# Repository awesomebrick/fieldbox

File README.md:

# fieldbox
Senior design project. FPGA-powered eurorack synthesis and audio processing module

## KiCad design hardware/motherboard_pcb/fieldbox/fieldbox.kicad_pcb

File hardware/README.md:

# Sorry for the mess.
Will sort things properly when I get the chance.

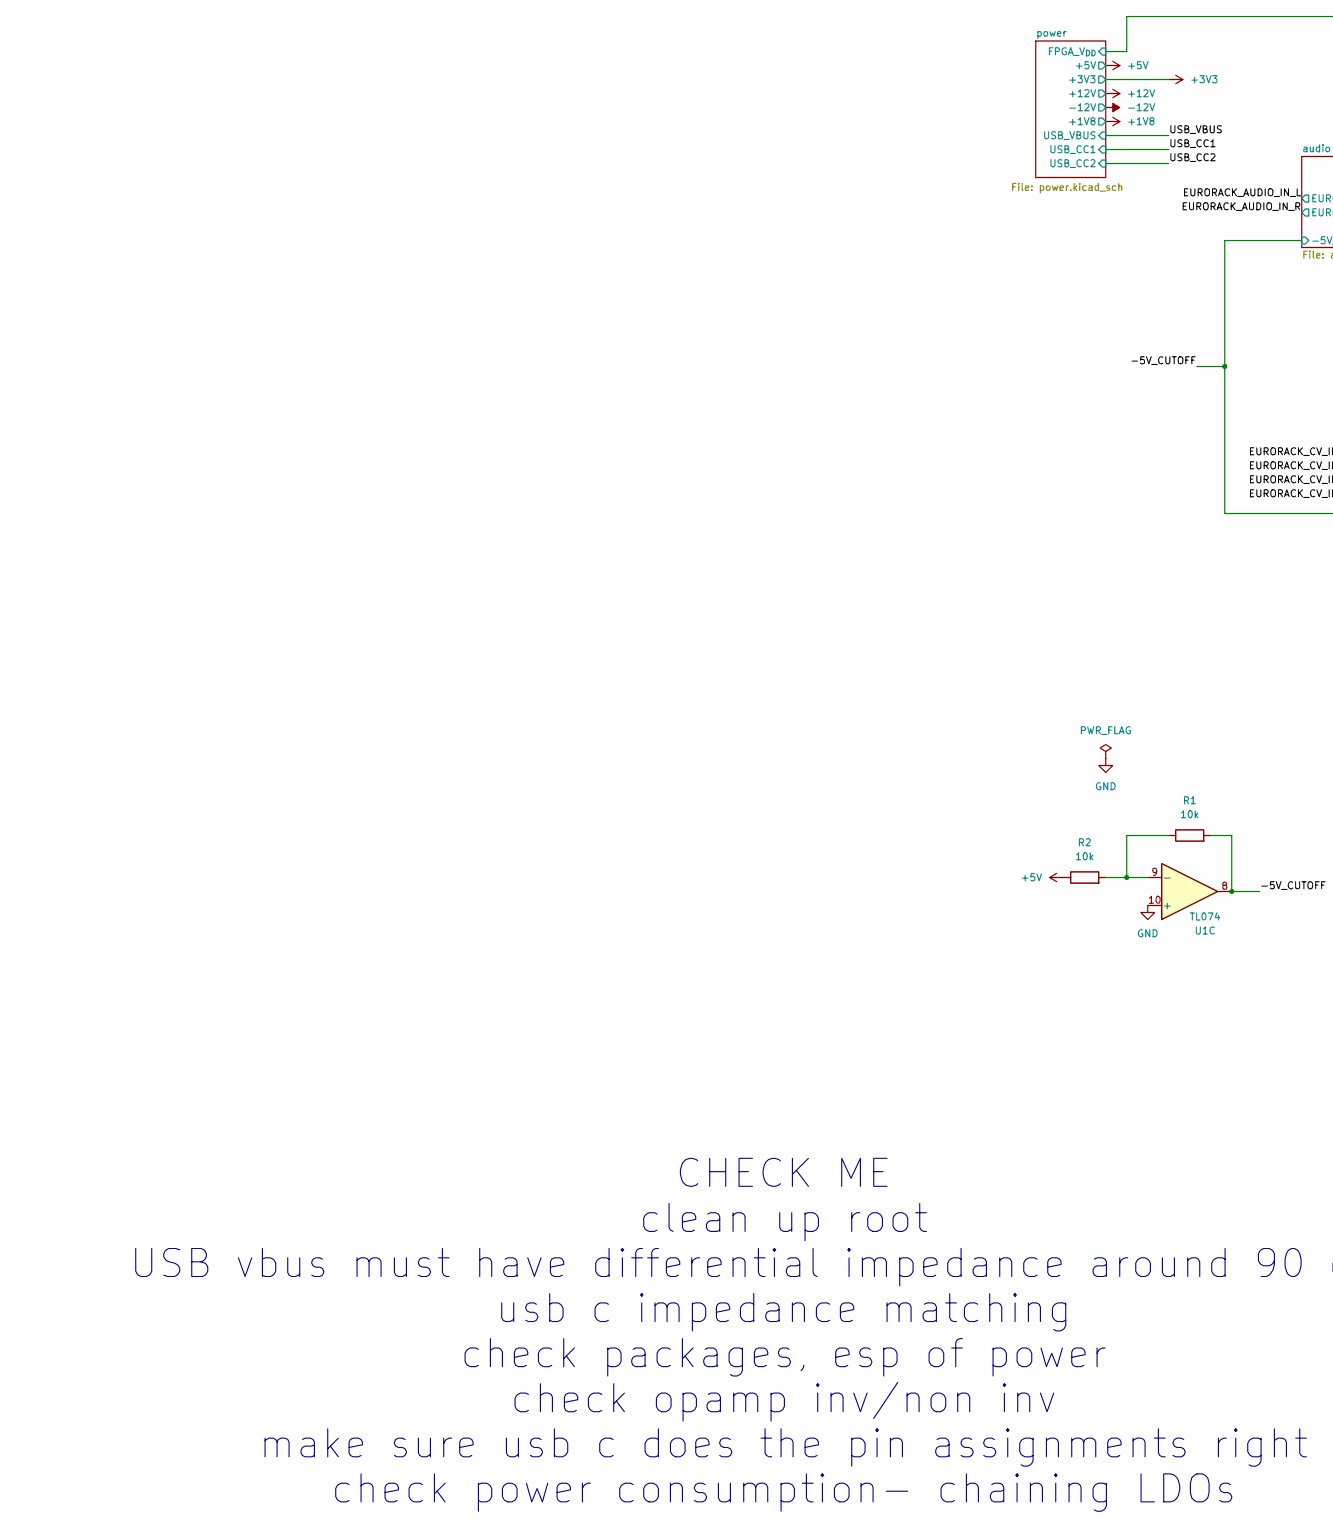
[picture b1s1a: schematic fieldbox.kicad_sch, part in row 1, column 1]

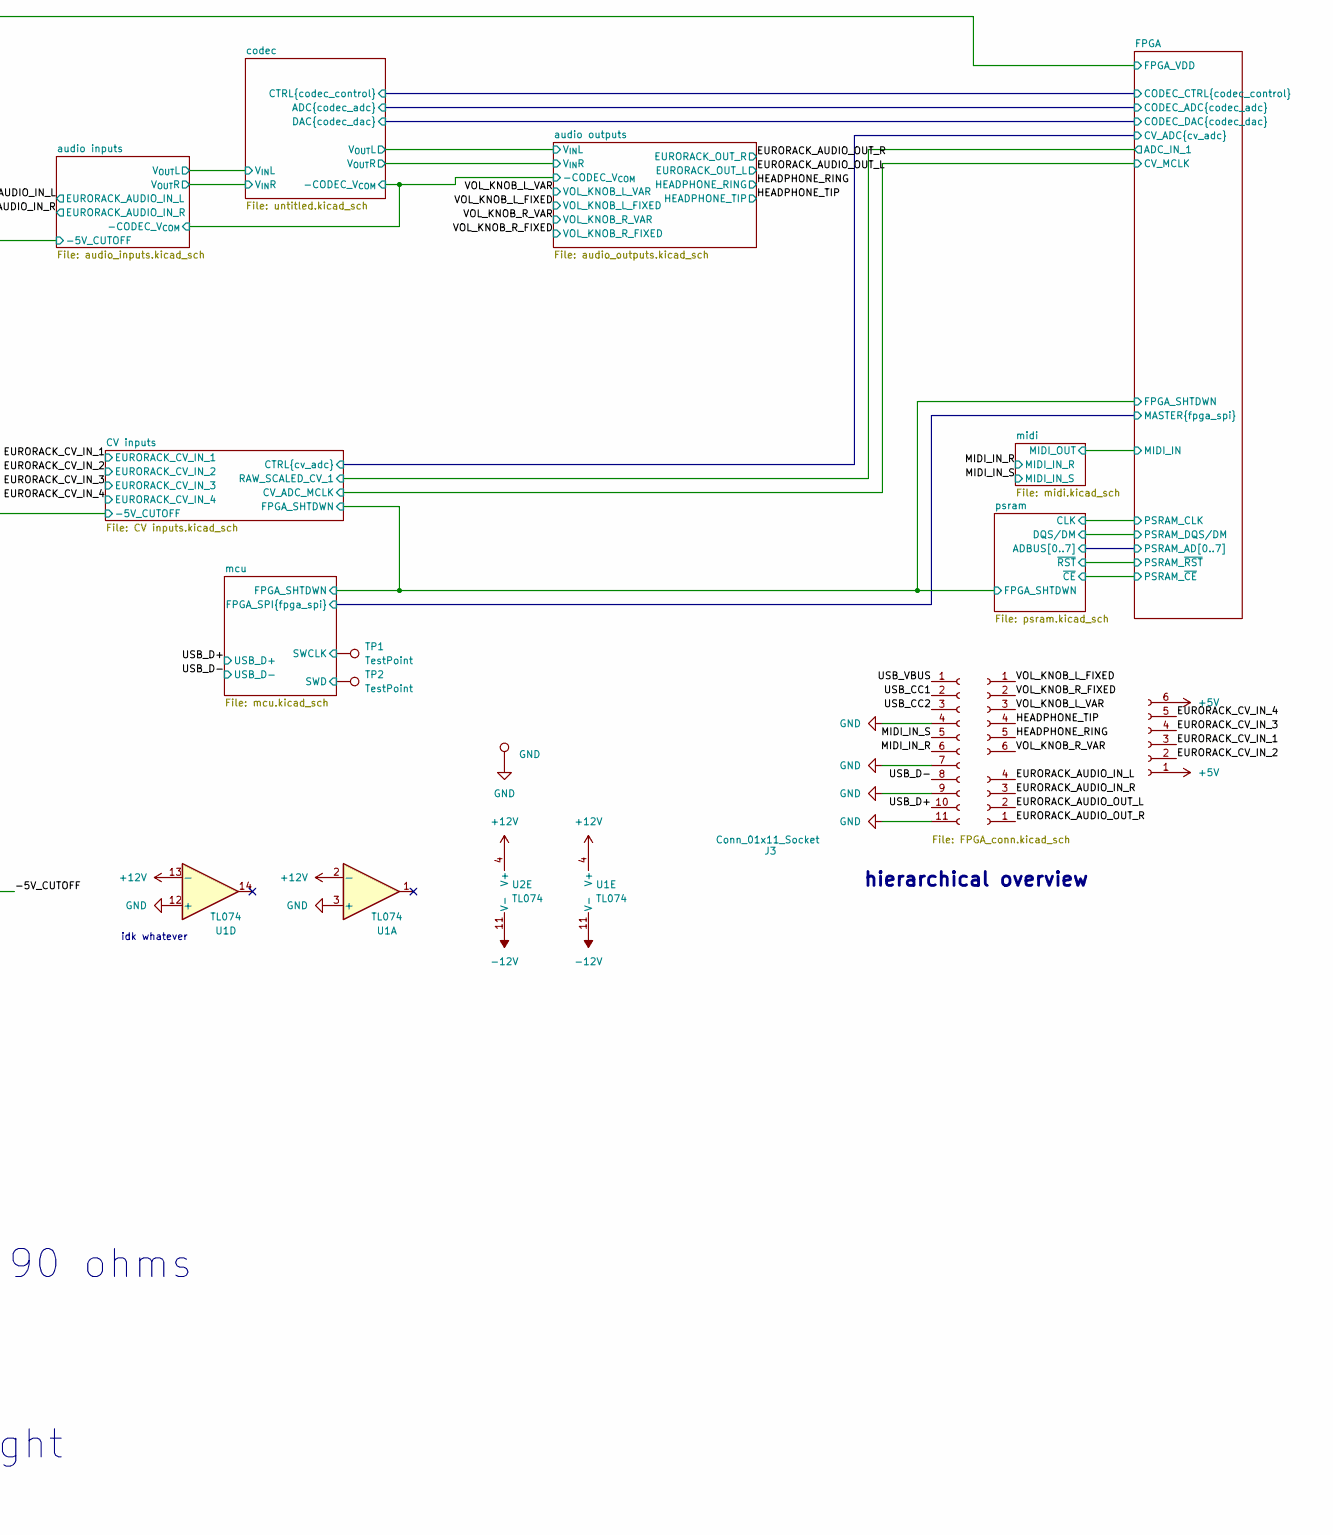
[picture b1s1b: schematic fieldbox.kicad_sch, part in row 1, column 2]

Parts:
J1: Conn_01x04_Socket; PinSocket_1x06_P2.54mm_Vertical
J2: Conn_01x06_Socket; PinSocket_1x06_P2.54mm_Vertical
J3: Conn_01x11_Socket; PinSocket_1x11_P2.54mm_Vertical
J5: Conn_01x04_Socket; PinSocket_1x04_P2.54mm_Vertical
R1, R2: 10k; R_0603_1608Metric; Mouser # 652-CRT0603BY1002ELF
TP1, TP2: TestPoint; TestPoint_Pad_2.0x2.0mm; Mouser # NA
TP3: GND; TestPoint_Pad_D2.0mm; Mouser # NA
U1, U2: TL074; TSSOP-14_4.4x5mm_P0.65mm; Mouser # 595-TL074HIPWR

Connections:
+5V: J1.1, J1.6, R2.1; also elsewhere on the board
+12V: U1.2 (-), U1.4 (V+), U1.13 (-), U2.4 (V+); also elsewhere on the board
-12V: U1.11 (V-), U2.11 (V-); also elsewhere on the board
/-5V_CUTOFF: R1.2, U1.8; also elsewhere on the board
/EURORACK_AUDIO_IN_L: J5.4; also elsewhere on the board
/EURORACK_AUDIO_IN_R: J5.3; also elsewhere on the board
/EURORACK_AUDIO_OUT_L: J5.2; also elsewhere on the board
/EURORACK_AUDIO_OUT_R: J5.1; also elsewhere on the board
/EURORACK_CV_IN_1: J1.3; also elsewhere on the board
/EURORACK_CV_IN_2: J1.2; also elsewhere on the board
/EURORACK_CV_IN_3: J1.4; also elsewhere on the board
/EURORACK_CV_IN_4: J1.5; also elsewhere on the board
/HEADPHONE_RING: J2.5; also elsewhere on the board
/HEADPHONE_TIP: J2.4; also elsewhere on the board
/MIDI_IN_R: J3.6; also elsewhere on the board
/MIDI_IN_S: J3.5; also elsewhere on the board
/USB_CC1: J3.2; also elsewhere on the board
/USB_CC2: J3.3; also elsewhere on the board
/USB_D+: J3.10; also elsewhere on the board
/USB_D-: J3.8; also elsewhere on the board
/USB_VBUS: J3.1; also elsewhere on the board
/VOL_KNOB_L_FIXED: J2.1; also elsewhere on the board
/VOL_KNOB_L_VAR: J2.3; also elsewhere on the board
/VOL_KNOB_R_FIXED: J2.2; also elsewhere on the board
/VOL_KNOB_R_VAR: J2.6; also elsewhere on the board
/mcu/SWCLK: TP1.1; also elsewhere on the board
/mcu/SWD: TP2.1; also elsewhere on the board
GND: J3.4, J3.7, J3.9, J3.11, TP3.1, U1.3 (+), U1.10 (+), U1.12 (+); also elsewhere on the board
unnamed: R1.1, R2.2, U1.9 (-)

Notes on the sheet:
hierarchical overview
CHECK ME clean up root USB vbus must have differential impedance around 90 ohms usb c impedance matching check packages, esp of power check opamp inv/non inv make sure usb c does the pin assignments right check power consumption- chaining LDOs
idk whatever

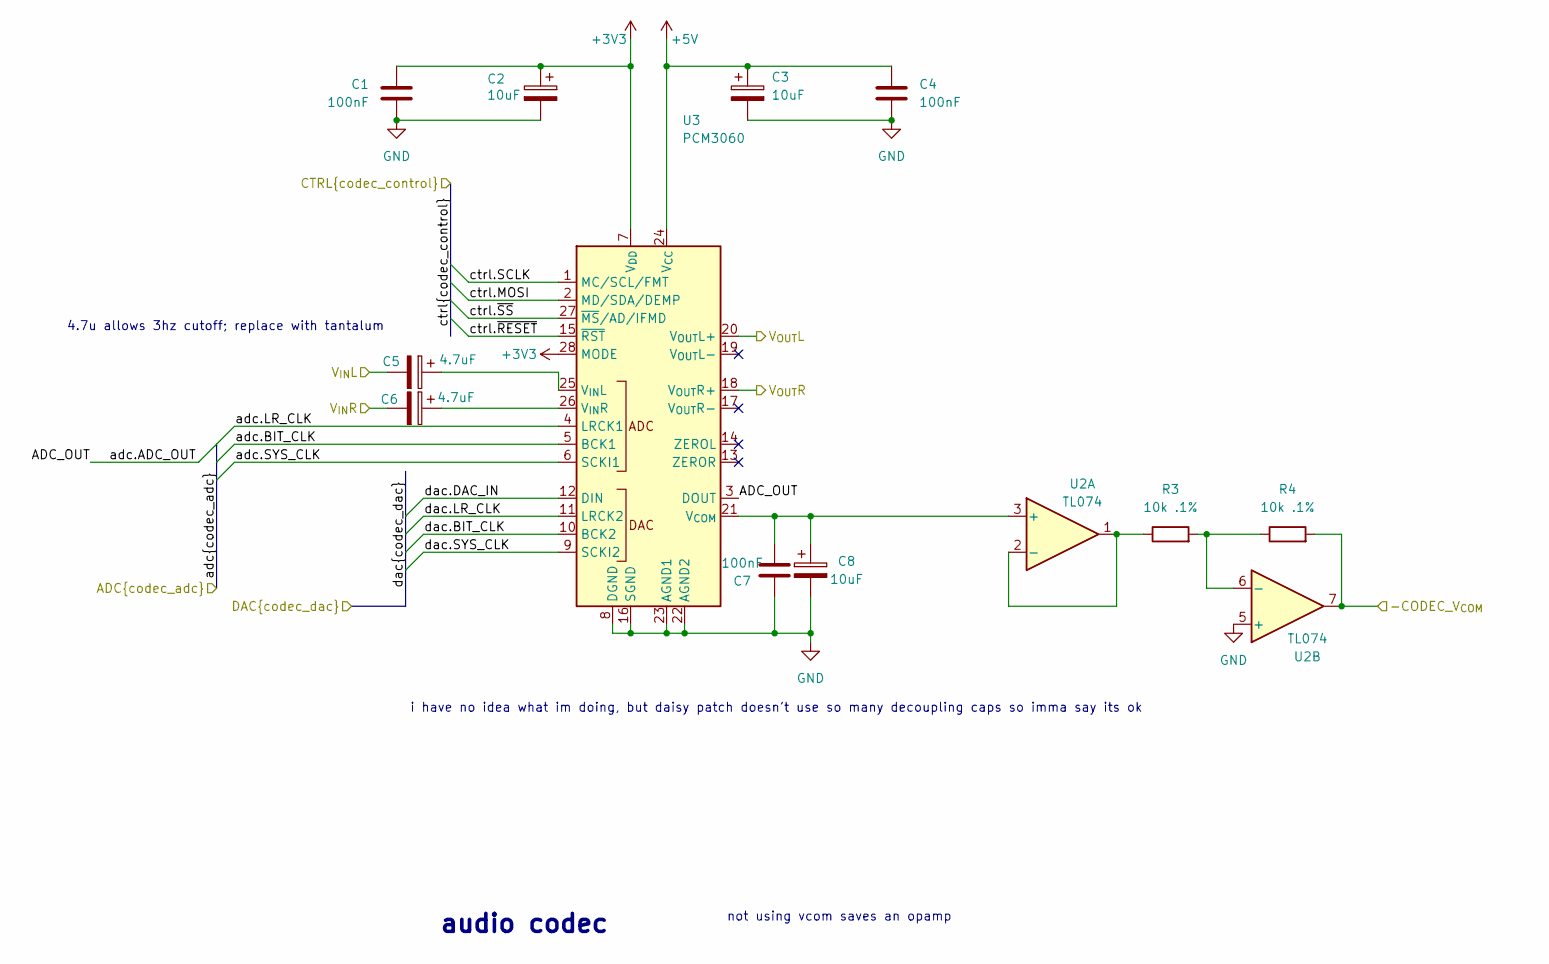
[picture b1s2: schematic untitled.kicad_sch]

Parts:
C1, C4, C7: 100nF; C_0603_1608Metric; Mouser # KGM15AR71C104MM
C2, C3, C8: 10uF; CP_EIA-3216-18_Kemet-A; Mouser # 581-TAJA106K016R
C5, C6: 4.7uF; CP_EIA-3216-18_Kemet-A; Mouser # 581-TAJA475M006R
R3, R4: 10k .1%; R_0603_1608Metric; Mouser # 652-CRT0603BY1002ELF
U2: TL074; TSSOP-14_4.4x5mm_P0.65mm; Mouser # 595-TL074HIPWR
U3: PCM3060; TSSOP-28_4.4x9.7mm_P0.65mm; Mouser # PCM3060PWR

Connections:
+3V3: C1.1, C2.1, U3.7 (V_{DD}), U3.28 (MODE); also elsewhere on the board
+5V: C3.1, C4.1, U3.24 (V_{CC}); also elsewhere on the board
/FPGA/CODEC_ADC.ADC_OUT: U3.3 (DOUT); also elsewhere on the board
/FPGA/CODEC_ADC.BIT_CLK: U3.5 (BCK1); also elsewhere on the board
/FPGA/CODEC_ADC.LR_CLK: U3.4 (LRCK1); also elsewhere on the board
/FPGA/CODEC_ADC.SYS_CLK: U3.6 (SCKI1); also elsewhere on the board
/FPGA/CODEC_CTRL.MOSI: U3.2 (MD/SDA/DEMP); also elsewhere on the board
/FPGA/CODEC_CTRL.SCLK: U3.1 (MC/SCL/FMT); also elsewhere on the board
/FPGA/CODEC_CTRL.~RESET: U3.15 (~RST); also elsewhere on the board
/FPGA/CODEC_CTRL.~SS: U3.27 (~MS/AD/IFMD); also elsewhere on the board
/FPGA/CODEC_DAC.BIT_CLK: U3.10 (BCK2); also elsewhere on the board
/FPGA/CODEC_DAC.DAC_IN: U3.12 (DIN); also elsewhere on the board
/FPGA/CODEC_DAC.LR_CLK: U3.11 (LRCK2); also elsewhere on the board
/FPGA/CODEC_DAC.SYS_CLK: U3.9 (SCKI2); also elsewhere on the board
/audio inputs/-CODEC_V_{COM}: R4.2, U2.7; also elsewhere on the board
/audio inputs/V_{OUT}L: C5.2; also elsewhere on the board
/audio inputs/V_{OUT}R: C6.2; also elsewhere on the board
/audio outputs/V_{IN}L: U3.20 (V_{OUT}L+); also elsewhere on the board
/audio outputs/V_{IN}R: U3.18 (V_{OUT}R+); also elsewhere on the board
GND: C1.2, C2.2, C3.2, C4.2, C7.1, C8.2, U2.5 (+), U3.8 (DGND), U3.16 (SGND), U3.22 (AGND2), U3.23 (AGND1); also elsewhere on the board
unnamed: C7.2, C8.1, U2.3 (+), U3.21 (V_{COM})
unnamed: R3.1, U2.1, U2.2 (-)
unnamed: R3.2, R4.1, U2.6 (-)
unnamed: C5.1, U3.25 (V_{IN}L)
unnamed: C6.1, U3.26 (V_{IN}R)

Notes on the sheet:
i have no idea what im doing, but daisy patch doesn't use so many decoupling caps so imma say its ok
4.7u allows 3hz cutoff; replace with tantalum
not using vcom saves an opamp
audio codec

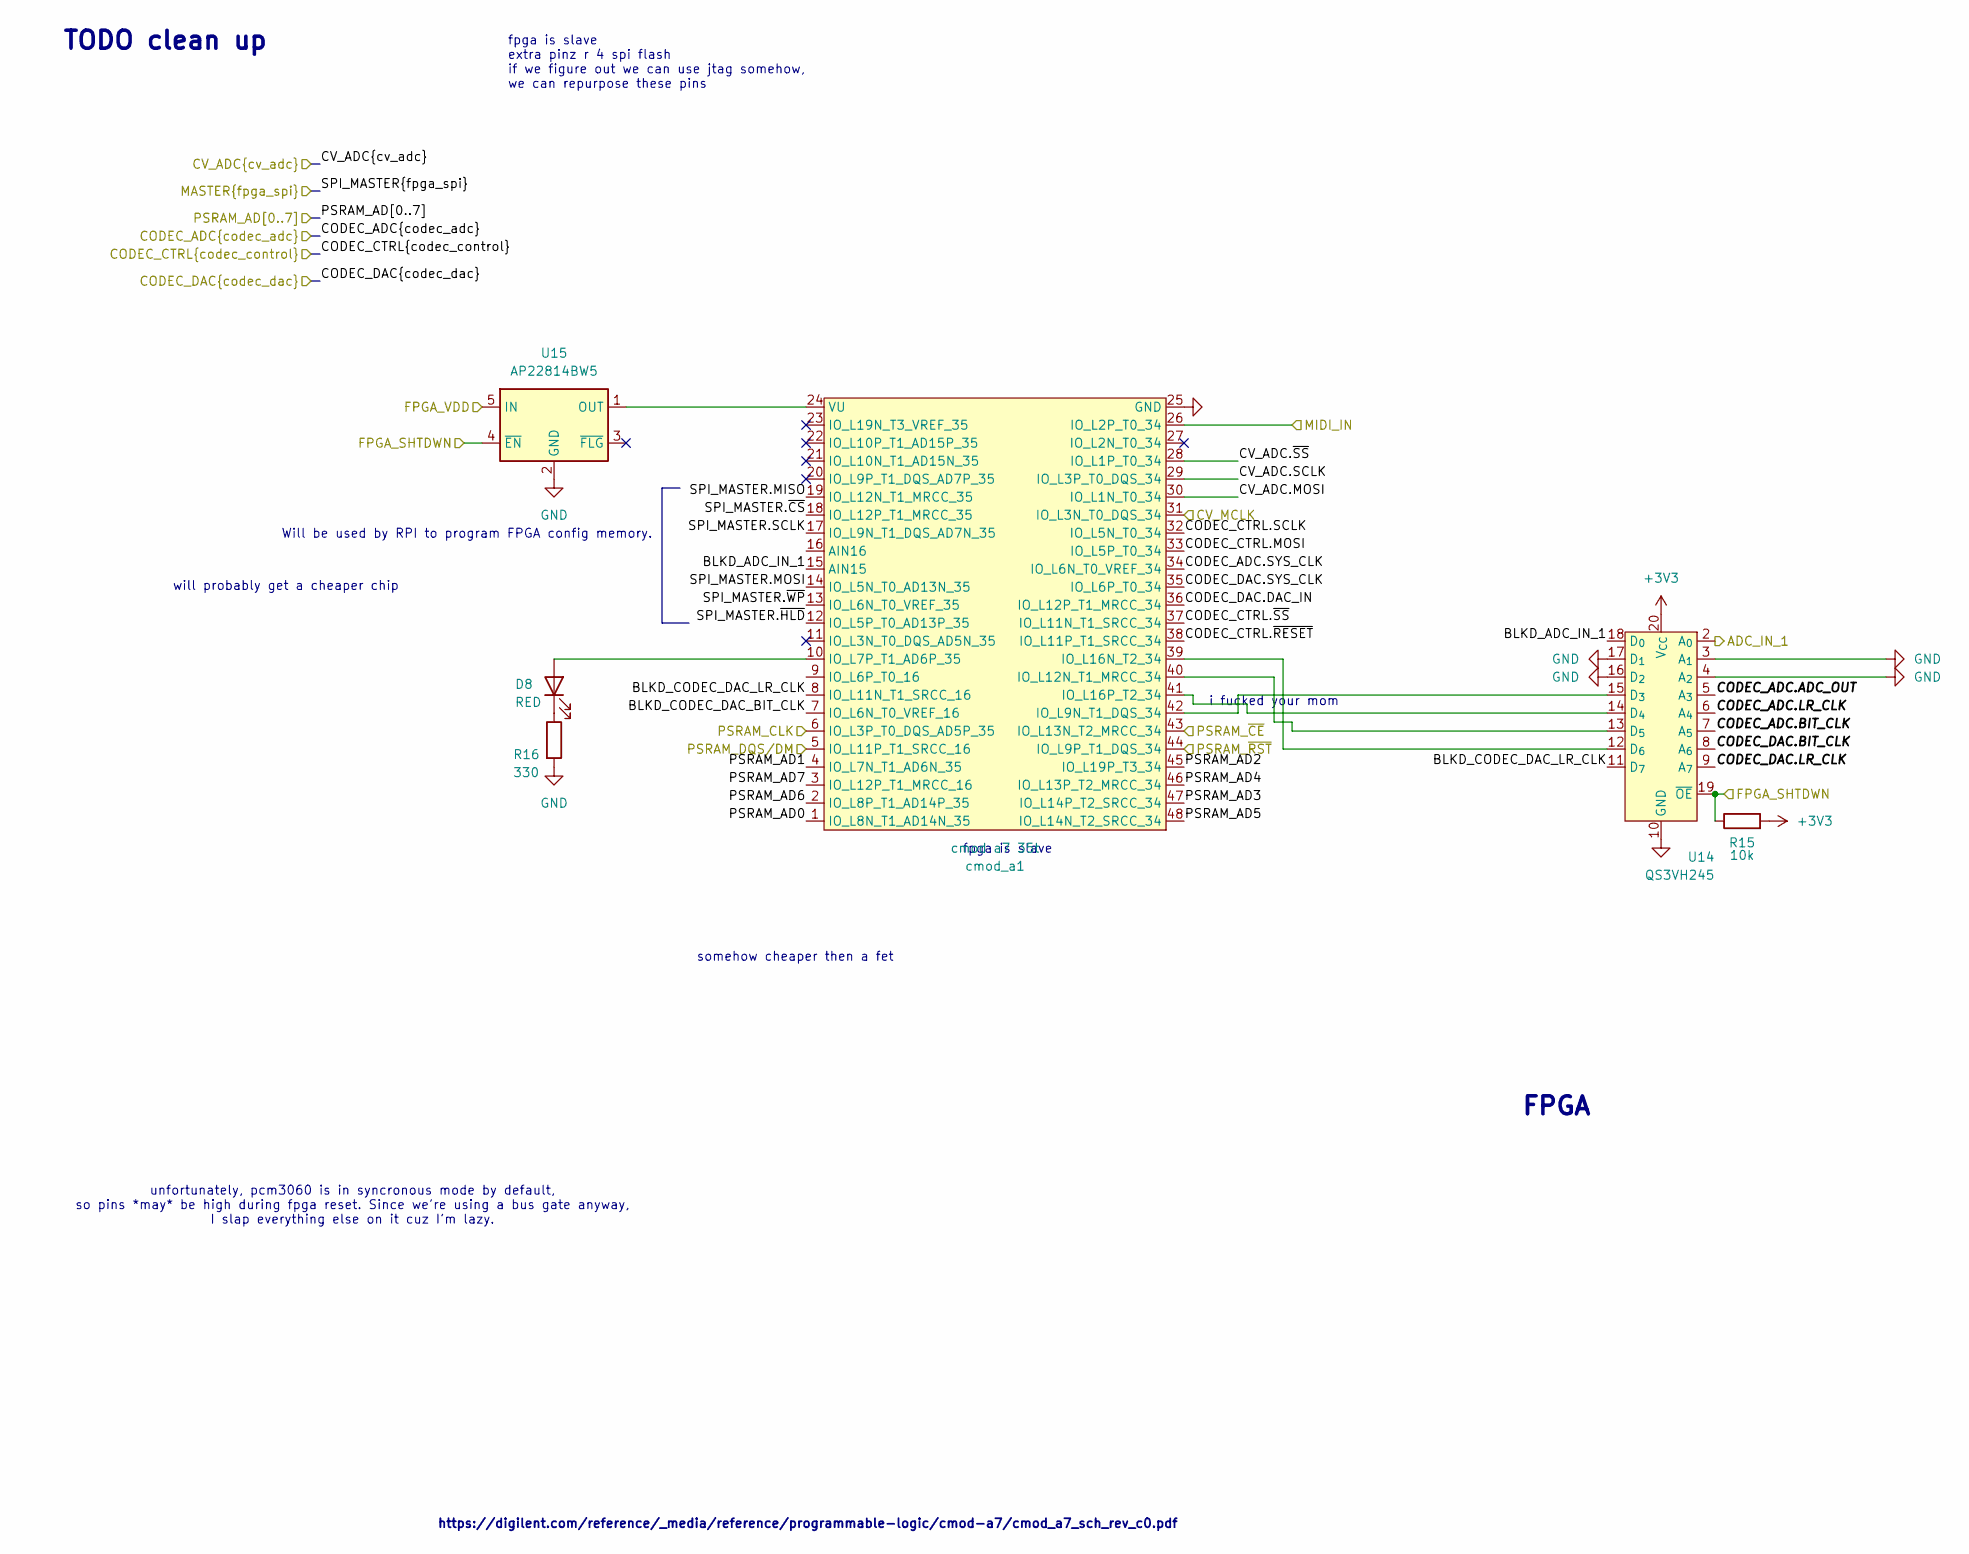
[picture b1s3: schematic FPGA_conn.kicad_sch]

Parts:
D8: RED; LED_0603_1608Metric; Mouser # 720-LSQ976.01-N1Q2-1
R15: 10k; R_0603_1608Metric; Mouser # 652-CRT0603BY1002ELF
R16: 330; R_0603_1608Metric; Mouser # 603-RC0603FR-10330RL
U14: QS3VH245; QSOP-20_3.9x8.7mm_P0.635mm; Mouser # 972-QS3VH245QG8
U15: AP22814BW5; SOT-23-5; Mouser # 621-AP22814BW5-7
cmod_a1: cmod a7 35t; CMOD-A7; Mouser # 424-410-328-35

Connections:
+3V3: R15.2, U14.20 (V_{CC}); also elsewhere on the board
/CV inputs/CV_ADC_MCLK: cmod_a1.31 (IO_L3N_T0_DQS_34); also elsewhere on the board
/CV inputs/FPGA_SHTDWN: R15.1, U14.19 (~OE), U15.4 (~EN); also elsewhere on the board
/CV inputs/RAW_SCALED_CV_1: U14.2 (A_{0}); also elsewhere on the board
/CV inputs/adc.MOSI: cmod_a1.30 (IO_L1N_T0_34); also elsewhere on the board
/CV inputs/adc.SCLK: cmod_a1.29 (IO_L3P_T0_DQS_34); also elsewhere on the board
/CV inputs/adc.~SS: cmod_a1.28 (IO_L1P_T0_34); also elsewhere on the board
/FPGA/BLKD_ADC_IN_1: U14.18 (D_{0}), cmod_a1.15 (AIN15)
/FPGA/BLKD_CODEC_DAC_BIT_CLK: cmod_a1.7 (IO_L6N_T0_VREF_16)
/FPGA/BLKD_CODEC_DAC_LR_CLK: U14.11 (D_{7}), cmod_a1.8 (IO_L11N_T1_SRCC_16)
/FPGA/CODEC_ADC.ADC_OUT: U14.5 (A_{3}); also elsewhere on the board
/FPGA/CODEC_ADC.BIT_CLK: U14.7 (A_{5}); also elsewhere on the board
/FPGA/CODEC_ADC.LR_CLK: U14.6 (A_{4}); also elsewhere on the board
/FPGA/CODEC_ADC.SYS_CLK: cmod_a1.34 (IO_L6N_T0_VREF_34); also elsewhere on the board
/FPGA/CODEC_CTRL.MOSI: cmod_a1.33 (IO_L5P_T0_34); also elsewhere on the board
/FPGA/CODEC_CTRL.SCLK: cmod_a1.32 (IO_L5N_T0_34); also elsewhere on the board
/FPGA/CODEC_CTRL.~RESET: cmod_a1.38 (IO_L11P_T1_SRCC_34); also elsewhere on the board
/FPGA/CODEC_CTRL.~SS: cmod_a1.37 (IO_L11N_T1_SRCC_34); also elsewhere on the board
/FPGA/CODEC_DAC.BIT_CLK: U14.8 (A_{6}); also elsewhere on the board
/FPGA/CODEC_DAC.DAC_IN: cmod_a1.36 (IO_L12P_T1_MRCC_34); also elsewhere on the board
/FPGA/CODEC_DAC.LR_CLK: U14.9 (A_{7}); also elsewhere on the board
/FPGA/CODEC_DAC.SYS_CLK: cmod_a1.35 (IO_L6P_T0_34); also elsewhere on the board
/FPGA/FPGA_VDD: U15.5 (IN); also elsewhere on the board
/FPGA/MIDI_IN: cmod_a1.26 (IO_L2P_T0_34); also elsewhere on the board
/FPGA/PSRAM_AD0: cmod_a1.1 (IO_L8N_T1_AD14N_35); also elsewhere on the board
/FPGA/PSRAM_AD1: cmod_a1.4 (IO_L7N_T1_AD6N_35); also elsewhere on the board
/FPGA/PSRAM_AD2: cmod_a1.45 (IO_L19P_T3_34); also elsewhere on the board
/FPGA/PSRAM_AD3: cmod_a1.47 (IO_L14P_T2_SRCC_34); also elsewhere on the board
/FPGA/PSRAM_AD4: cmod_a1.46 (IO_L13P_T2_MRCC_34); also elsewhere on the board
/FPGA/PSRAM_AD5: cmod_a1.48 (IO_L14N_T2_SRCC_34); also elsewhere on the board
/FPGA/PSRAM_AD6: cmod_a1.2 (IO_L8P_T1_AD14P_35); also elsewhere on the board
/FPGA/PSRAM_AD7: cmod_a1.3 (IO_L12P_T1_MRCC_16); also elsewhere on the board
/FPGA/PSRAM_CLK: cmod_a1.6 (IO_L3P_T0_DQS_AD5P_35); also elsewhere on the board
/FPGA/PSRAM_DQS/DM: cmod_a1.5 (IO_L11P_T1_SRCC_16); also elsewhere on the board
/FPGA/PSRAM_~CE: cmod_a1.43 (IO_L13N_T2_MRCC_34); also elsewhere on the board
/FPGA/PSRAM_~RST: cmod_a1.44 (IO_L9P_T1_DQS_34); also elsewhere on the board
/FPGA/SPI_MASTER.MISO: cmod_a1.19 (IO_L12N_T1_MRCC_35); also elsewhere on the board
/FPGA/SPI_MASTER.MOSI: cmod_a1.14 (IO_L5N_T0_AD13N_35); also elsewhere on the board
/FPGA/SPI_MASTER.SCLK: cmod_a1.17 (IO_L9N_T1_DQS_AD7N_35); also elsewhere on the board
/FPGA/SPI_MASTER.~CS: cmod_a1.18 (IO_L12P_T1_MRCC_35); also elsewhere on the board
/FPGA/SPI_MASTER.~HLD: cmod_a1.12 (IO_L5P_T0_AD13P_35); also elsewhere on the board
/FPGA/SPI_MASTER.~WP: cmod_a1.13 (IO_L6N_T0_VREF_35); also elsewhere on the board
GND: R16.2, U14.3 (A_{1}), U14.4 (A_{2}), U14.10 (GND), U14.16 (D_{2}), U14.17 (D_{1}), U15.2 (GND), cmod_a1.25 (GND); also elsewhere on the board
unnamed: D8.2 (A), cmod_a1.10 (IO_L7P_T1_AD6P_35)
unnamed: D8.1 (K), R16.1
unnamed: U14.15 (D_{3}), cmod_a1.42 (IO_L9N_T1_DQS_34)
unnamed: U14.14 (D_{4}), cmod_a1.41 (IO_L16P_T2_34)
unnamed: U14.13 (D_{5}), cmod_a1.40 (IO_L12N_T1_MRCC_34)
unnamed: U14.12 (D_{6}), cmod_a1.39 (IO_L16N_T2_34)
unnamed: U15.1 (OUT), cmod_a1.24 (VU)

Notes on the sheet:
unfortunately, pcm3060 is in syncronous mode by default, so pins *may* be high during fpga reset. Since we're using a bus gate anyway, I slap everything else on it cuz I'm lazy.
fpga is slave
fpga is slave extra pinz r 4 spi flash if we figure out we can use jtag somehow, we can repurpose these pins
FPGA
TODO clean up
https://digilent.com/reference/_media/reference/programmable-logic/cmod-a7/cmod_a7_sch_rev_c0.pdf
will probably get a cheaper chip
Will be used by RPI to program FPGA config memory.
i fucked your mom
somehow cheaper then a fet

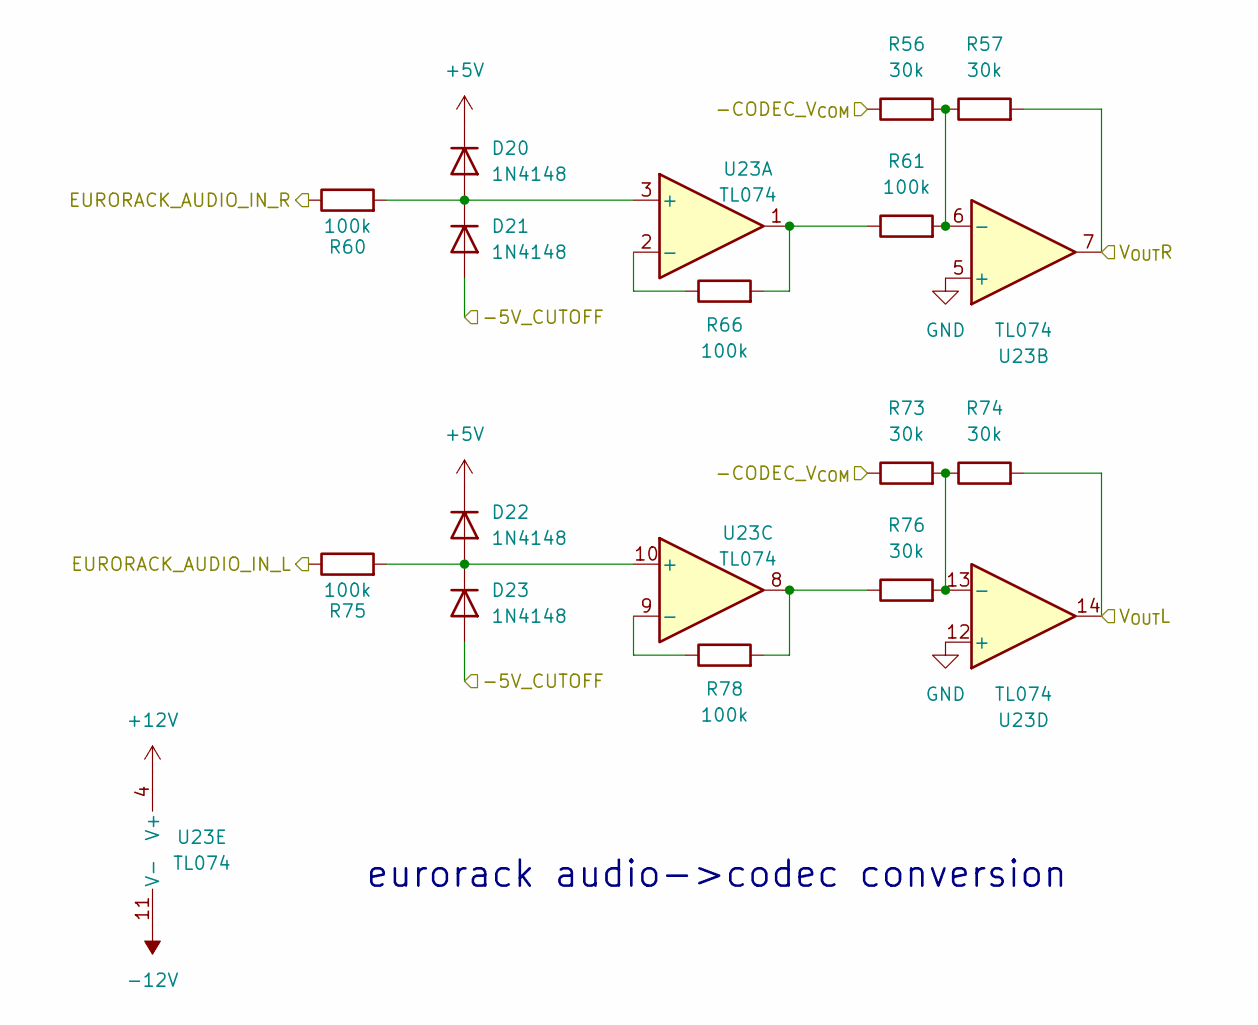
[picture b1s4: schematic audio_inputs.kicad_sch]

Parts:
D20, D21, D22, D23: 1N4148; D_SOD-323F; Mouser # 637-1N4148WS-AQ
R56, R57, R73, R74, R76: 30k; C_0603_1608Metric; Mouser # 660-RK73H1JTTDD3002F
R60, R61, R66, R75, R78: 100k; R_0603_1608Metric; Mouser # CR0603-FX-1003ELF
U23: TL074; TSSOP-14_4.4x5mm_P0.65mm; Mouser # 595-TL074HIPWR

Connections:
+5V: D20.1 (K), D22.1 (K); also elsewhere on the board
+12V: U23.4 (V+); also elsewhere on the board
-12V: U23.11 (V-); also elsewhere on the board
/-5V_CUTOFF: D21.2 (A), D23.2 (A); also elsewhere on the board
/EURORACK_AUDIO_IN_L: R75.1; also elsewhere on the board
/EURORACK_AUDIO_IN_R: R60.1; also elsewhere on the board
/audio inputs/-CODEC_V_{COM}: R56.1, R73.1; also elsewhere on the board
/audio inputs/V_{OUT}L: R74.2, U23.14; also elsewhere on the board
/audio inputs/V_{OUT}R: R57.2, U23.7; also elsewhere on the board
GND: U23.5 (+), U23.12 (+); also elsewhere on the board
unnamed: D20.2 (A), D21.1 (K), R60.2, U23.3 (+)
unnamed: D22.2 (A), D23.1 (K), R75.2, U23.10 (+)
unnamed: R61.1, R66.2, U23.1
unnamed: R76.1, R78.2, U23.8
unnamed: R66.1, U23.2 (-)
unnamed: R56.2, R57.1, R61.2, U23.6 (-)
unnamed: R78.1, U23.9 (-)
unnamed: R73.2, R74.1, R76.2, U23.13 (-)

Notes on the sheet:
eurorack audio->codec conversion

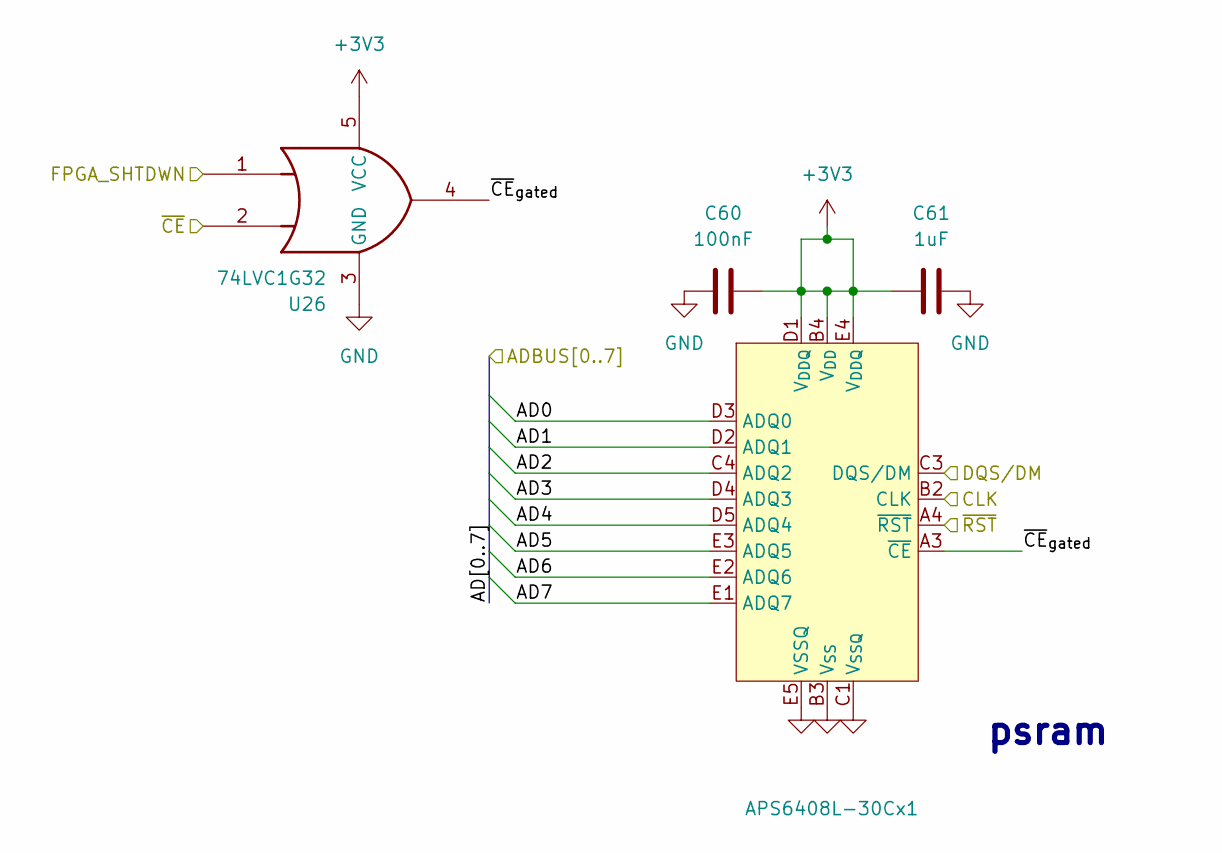
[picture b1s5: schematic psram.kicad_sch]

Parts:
APS6408L-30Cx1: BGA-24_6x8mm_Layout5x5_P1.0mm; Mouser # 878-APS6408L-3OC-BA
C60: 100nF; C_0603_1608Metric; Mouser # KGM15AR71C104MM
C61: 1uF; C_0603_1608Metric; Mouser # 791-0201X105M6R3CT
U26: 74LVC1G32; SOT-353_SC-70-5; Mouser # 771-74LVC1G32GW-G

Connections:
+3V3: APS6408L-30Cx1.B4 (V_{DD}), APS6408L-30Cx1.D1 (V_{DDQ}), APS6408L-30Cx1.E4 (V_{DDQ}), C60.2, C61.1, U26.5 (VCC); also elsewhere on the board
/CV inputs/FPGA_SHTDWN: U26.1; also elsewhere on the board
/FPGA/PSRAM_AD0: APS6408L-30Cx1.D3 (ADQ0); also elsewhere on the board
/FPGA/PSRAM_AD1: APS6408L-30Cx1.D2 (ADQ1); also elsewhere on the board
/FPGA/PSRAM_AD2: APS6408L-30Cx1.C4 (ADQ2); also elsewhere on the board
/FPGA/PSRAM_AD3: APS6408L-30Cx1.D4 (ADQ3); also elsewhere on the board
/FPGA/PSRAM_AD4: APS6408L-30Cx1.D5 (ADQ4); also elsewhere on the board
/FPGA/PSRAM_AD5: APS6408L-30Cx1.E3 (ADQ5); also elsewhere on the board
/FPGA/PSRAM_AD6: APS6408L-30Cx1.E2 (ADQ6); also elsewhere on the board
/FPGA/PSRAM_AD7: APS6408L-30Cx1.E1 (ADQ7); also elsewhere on the board
/FPGA/PSRAM_CLK: APS6408L-30Cx1.B2 (CLK); also elsewhere on the board
/FPGA/PSRAM_DQS/DM: APS6408L-30Cx1.C3 (DQS/DM); also elsewhere on the board
/FPGA/PSRAM_~CE: U26.2; also elsewhere on the board
/FPGA/PSRAM_~RST: APS6408L-30Cx1.A4 (~RST); also elsewhere on the board
/psram/~CE_{gated}: APS6408L-30Cx1.A3 (~CE), U26.4
GND: APS6408L-30Cx1.B3 (V_{SS}), APS6408L-30Cx1.C1 (V_{SSQ}), APS6408L-30Cx1.E5 (VSSQ), C60.1, C61.2, U26.3 (GND); also elsewhere on the board

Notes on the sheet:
psram

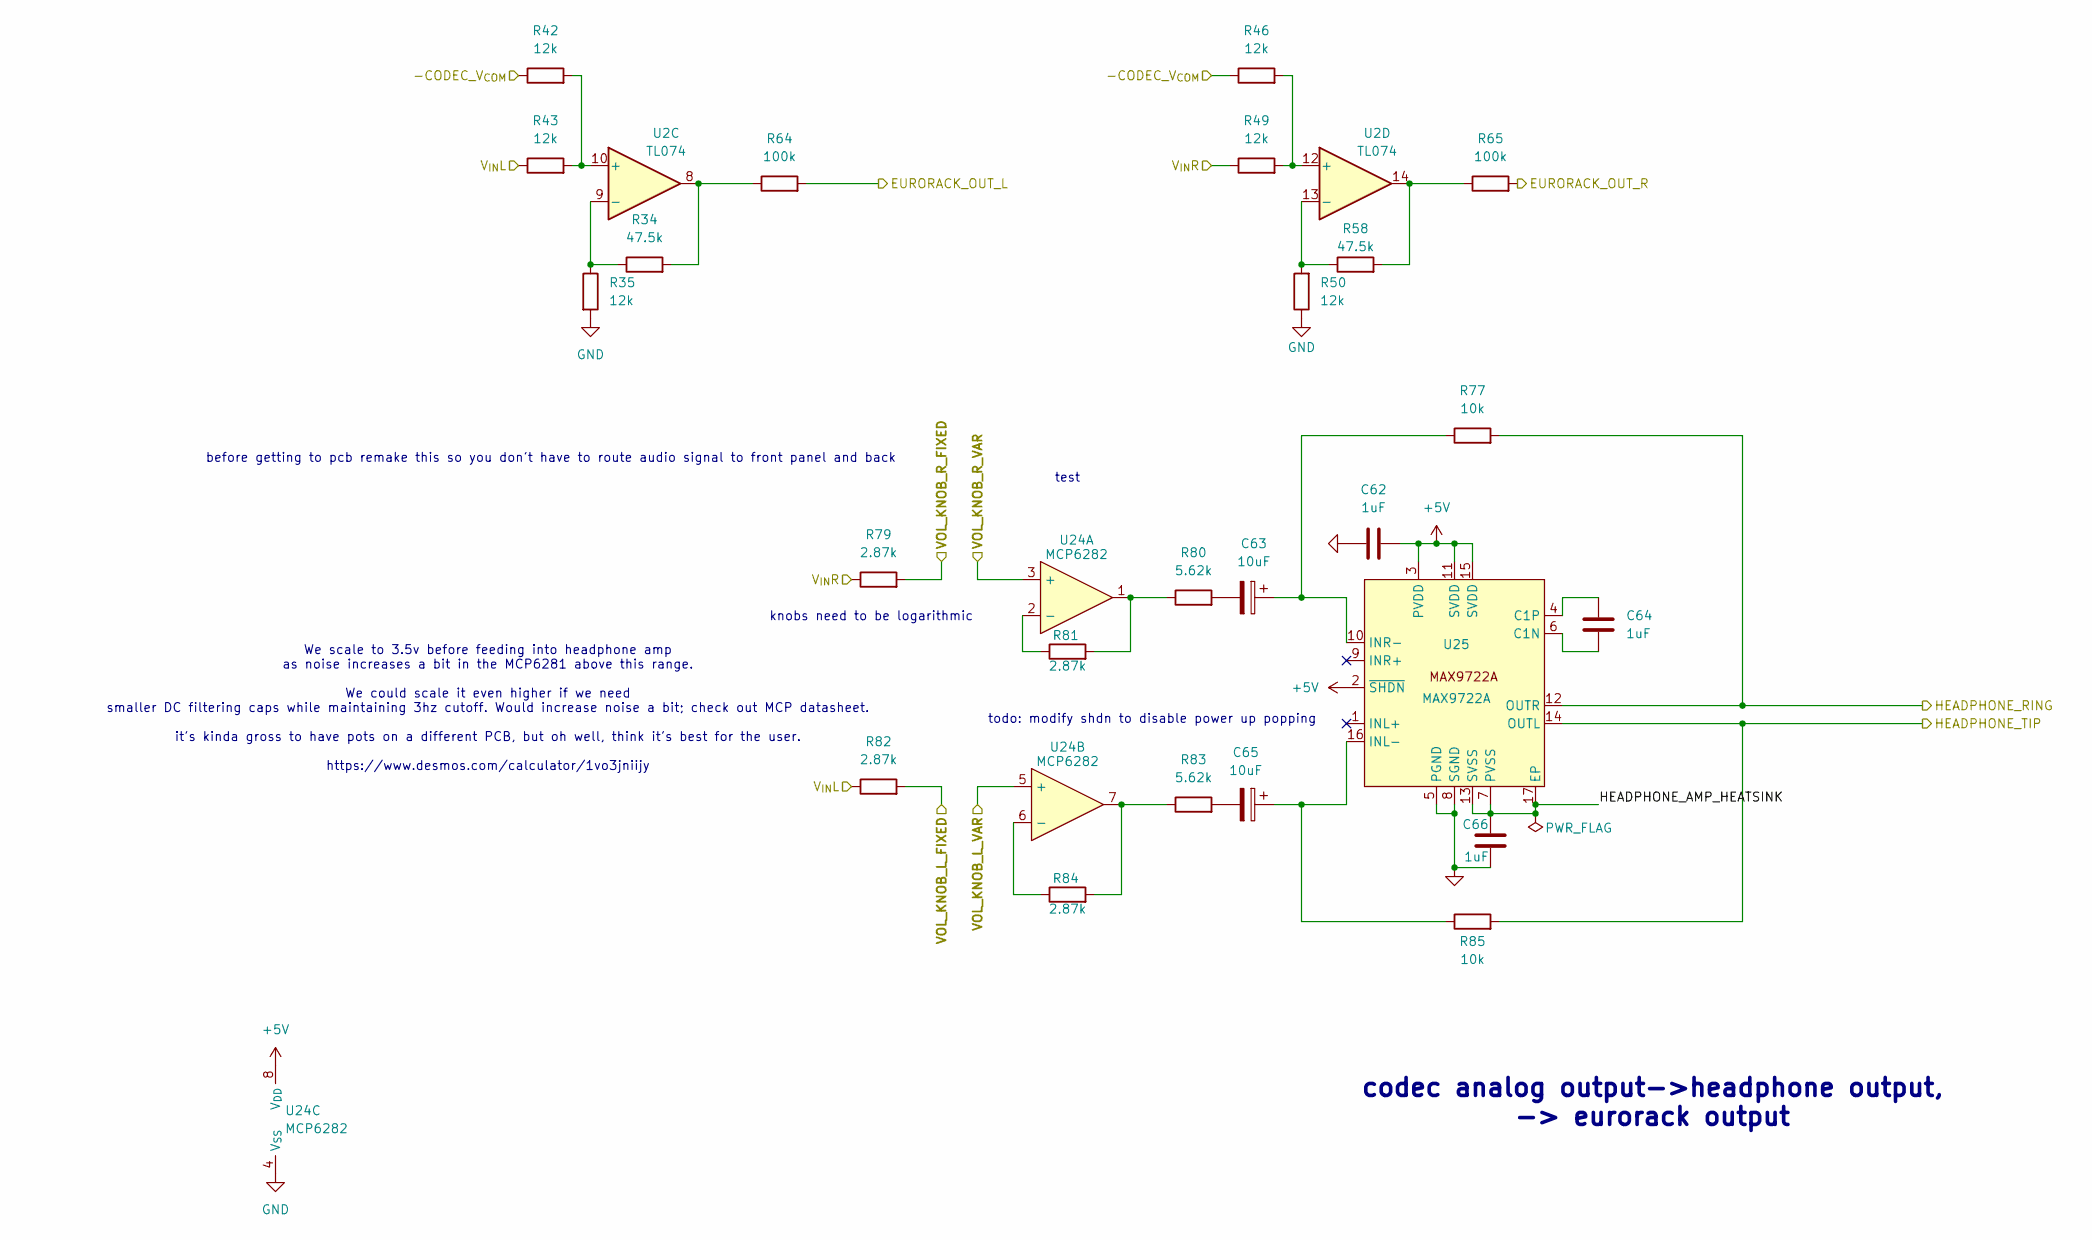
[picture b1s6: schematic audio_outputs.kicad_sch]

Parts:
C62, C64, C66: 1uF; C_0603_1608Metric; Mouser # 791-0201X105M6R3CT
C63, C65: 10uF; CP_EIA-3216-18_Kemet-A; Mouser # 581-TAJA106K016R
R34, R58: 47.5k; R_0603_1608Metric; Mouser # 667-ERA-3AEB4752V
R35, R42, R43, R46, R49, R50: 12k; R_0603_1608Metric; Mouser # 754-RG1608P-123-B-T5
R64, R65: 100k; R_0603_1608Metric; Mouser # CR0603-FX-1003ELF
R77, R85: 10k; R_0603_1608Metric; Mouser # 652-CRT0603BY1002ELF
R79, R81, R82, R84: 2.87k; R_0603_1608Metric; Mouser # 652-CR0603FX-2871ELF
R80, R83: 5.62k; R_0603_1608Metric; Mouser # 660-RK73H1JTTD5621F
U2: TL074; TSSOP-14_4.4x5mm_P0.65mm; Mouser # 595-TL074HIPWR
U24: MCP6282; MSOP-8_3x3mm_P0.65mm; Mouser # MCP6282T-E/MS
U25: MAX9722A; TSSOP-16-1EP_4.4x5mm_P0.65mm_EP3x3mm; Mouser # 700-MAX9722AEUE

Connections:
+5V: C62.2, U24.8 (V_{DD}), U25.2 (~SHDN), U25.3 (PVDD), U25.11 (SVDD), U25.15 (SVDD); also elsewhere on the board
/EURORACK_AUDIO_OUT_L: R64.2; also elsewhere on the board
/EURORACK_AUDIO_OUT_R: R65.2; also elsewhere on the board
/HEADPHONE_RING: R77.2, U25.12 (OUTR); also elsewhere on the board
/HEADPHONE_TIP: R85.2, U25.14 (OUTL); also elsewhere on the board
/VOL_KNOB_L_FIXED: R82.2; also elsewhere on the board
/VOL_KNOB_L_VAR: U24.5 (+); also elsewhere on the board
/VOL_KNOB_R_FIXED: R79.2; also elsewhere on the board
/VOL_KNOB_R_VAR: U24.3 (+); also elsewhere on the board
/audio inputs/-CODEC_V_{COM}: R42.1, R46.1; also elsewhere on the board
/audio outputs/HEADPHONE_AMP_HEATSINK: C66.1, U25.7 (PVSS), U25.13 (SVSS), U25.17 (EP)
/audio outputs/V_{IN}L: R43.1, R82.1; also elsewhere on the board
/audio outputs/V_{IN}R: R49.1, R79.1; also elsewhere on the board
GND: C62.1, C66.2, R35.2, R50.1, U24.4 (V_{SS}), U25.5 (PGND), U25.8 (SGND); also elsewhere on the board
unnamed: C63.2, R80.2
unnamed: C65.2, R83.2
unnamed: R34.2, R64.1, U2.8
unnamed: R58.2, R65.1, U2.14
unnamed: R80.1, R81.2, U24.1
unnamed: R83.1, R84.2, U24.7
unnamed: R42.2, R43.2, U2.10 (+)
unnamed: R34.1, R35.1, U2.9 (-)
unnamed: R46.2, R49.2, U2.12 (+)
unnamed: R50.2, R58.1, U2.13 (-)
unnamed: R81.1, U24.2 (-)
unnamed: R84.1, U24.6 (-)
unnamed: C64.2, U25.6 (C1N)
unnamed: C64.1, U25.4 (C1P)
unnamed: C65.1, R85.1, U25.16 (INL-)
unnamed: C63.1, R77.1, U25.10 (INR-)

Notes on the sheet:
codec analog output->headphone output, -> eurorack output
todo: modify shdn to disable power up popping
knobs need to be logarithmic
We scale to 3.5v before feeding into headphone amp as noise increases a bit in the MCP6281 above this range. We could scale it even higher if we need smaller DC filtering caps while maintaining 3hz cutoff. Would increase noise a bit; check out MCP datasheet. it's kinda gross to have pots on a diffe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
test
before getting to pcb remake this so you don't have to route audio signal to front panel and back
